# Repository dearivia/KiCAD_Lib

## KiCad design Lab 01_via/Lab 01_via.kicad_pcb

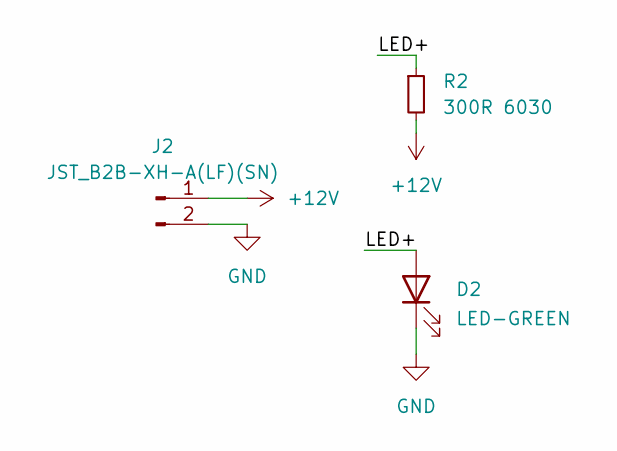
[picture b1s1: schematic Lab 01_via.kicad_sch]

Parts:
D2: LED-GREEN; LED_0603_1608Metric_Pad1.05x0.95mm_HandSolder; MPN LTST-C190GKT; Digikey PN 160-1183-1-ND
J2: JST_B2B-XH-A(LF)(SN); JST_B2B-XH-A_LF__SN_; MPN B2B-XH-A; Digikey PN 455-B2B-XH-A-ND
R2: 300R 6030; R_0603_1608Metric_Pad0.98x0.95mm_HandSolder

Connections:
+12V: J2.1, R2.2
/LED+: D2.2 (A), R2.1
GND: D2.1 (K), J2.2

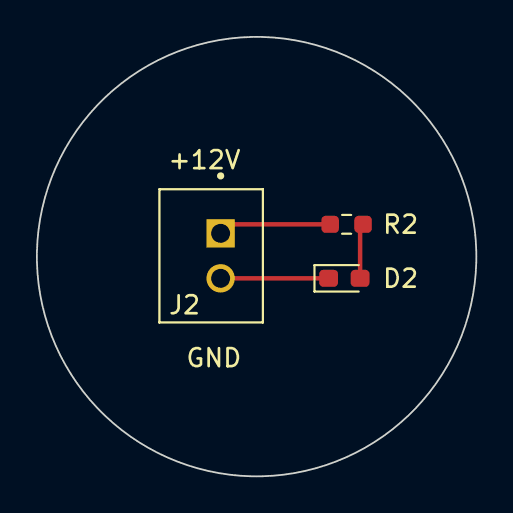
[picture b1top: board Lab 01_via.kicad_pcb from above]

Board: 2 copper layers, 24.4 x 24.4 mm, 3 parts (0 on the bottom side), 3 nets.

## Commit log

2024-01-11 assignment 2 schematic wip
    sry its so bad
2024-01-11 assignment 2 pls
    this is gonna explode
2024-01-12 sob
    sds
